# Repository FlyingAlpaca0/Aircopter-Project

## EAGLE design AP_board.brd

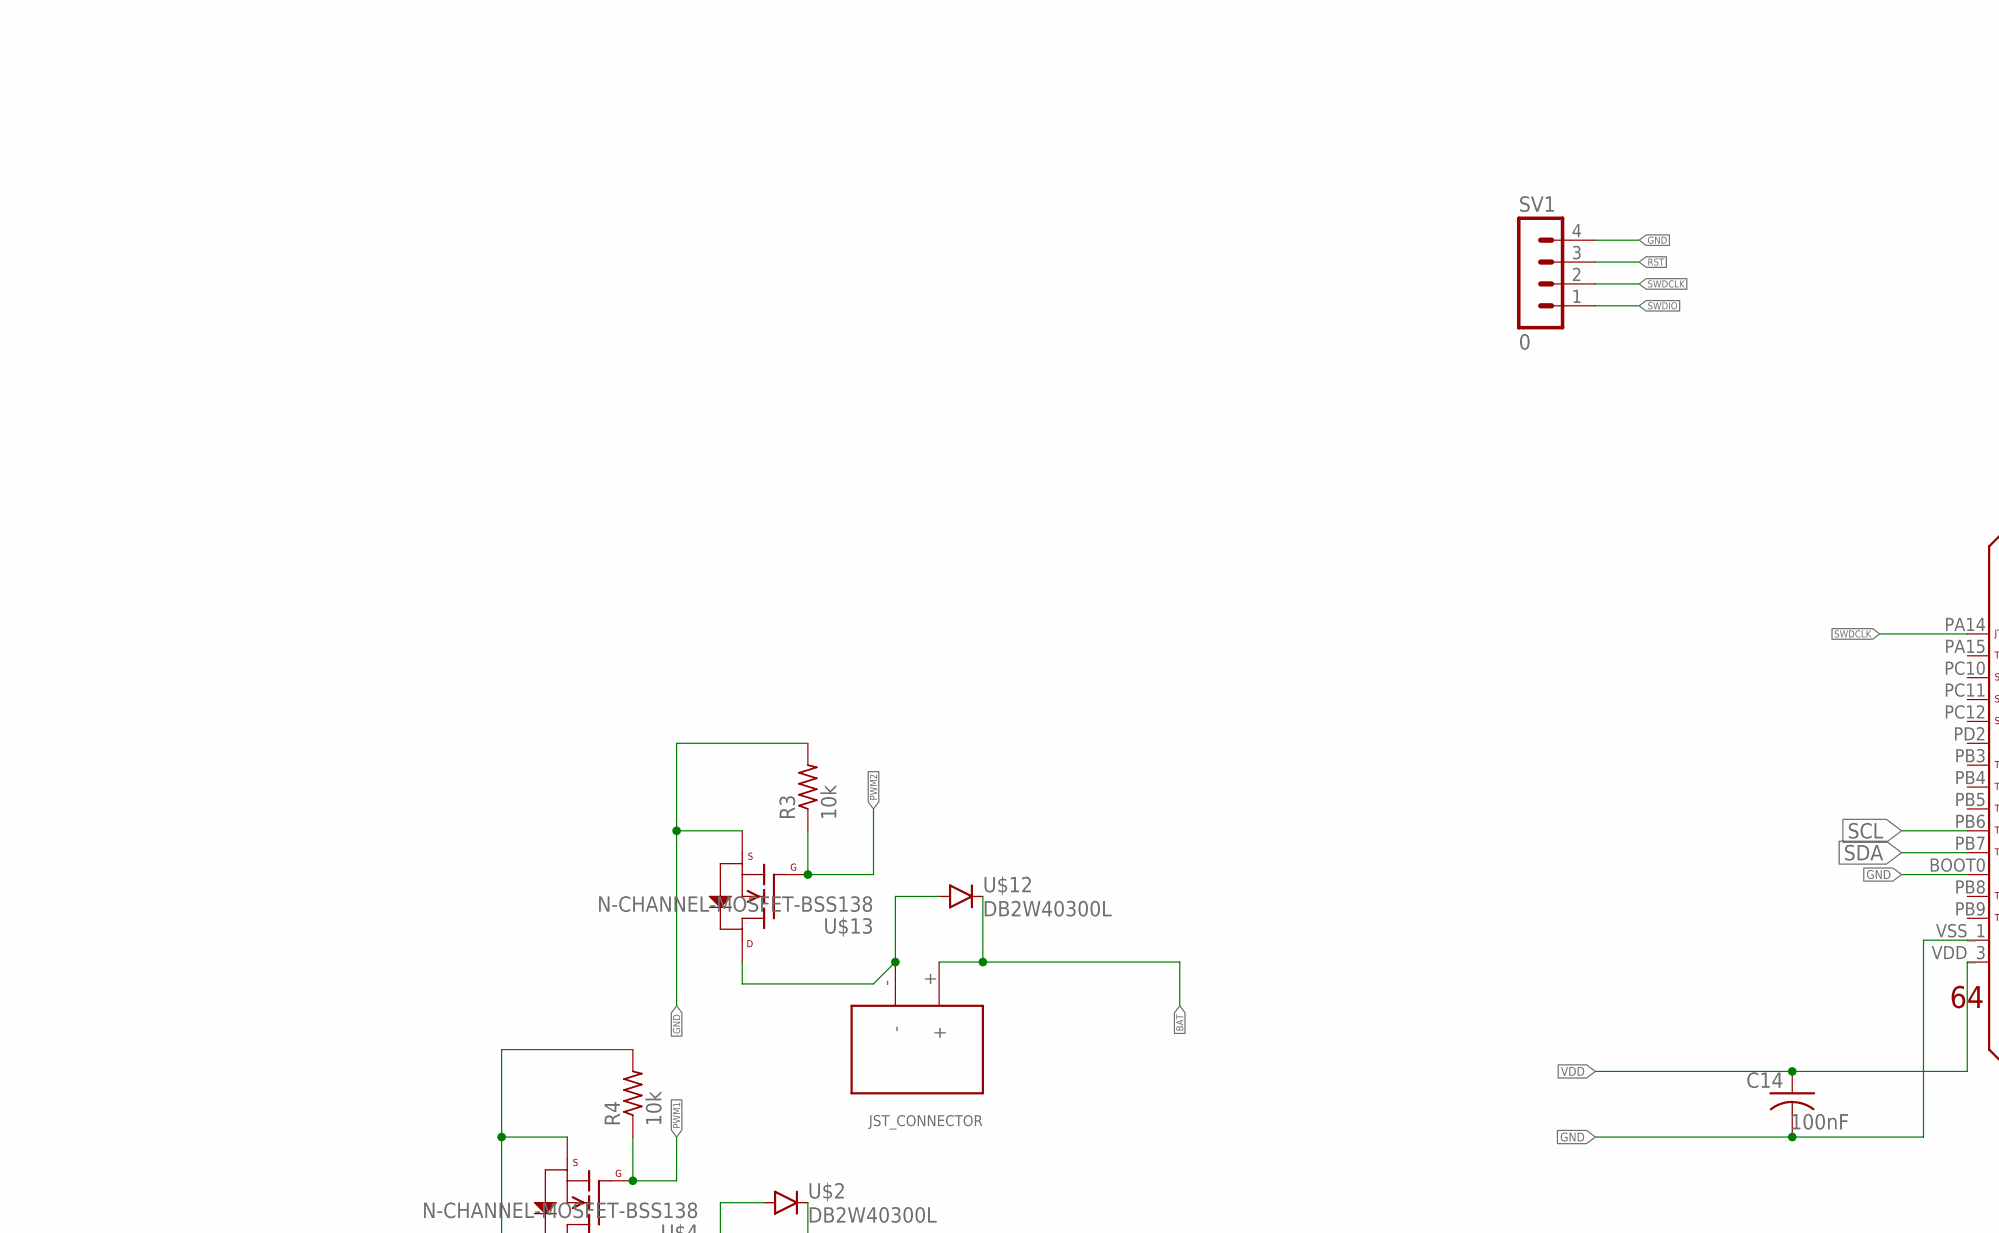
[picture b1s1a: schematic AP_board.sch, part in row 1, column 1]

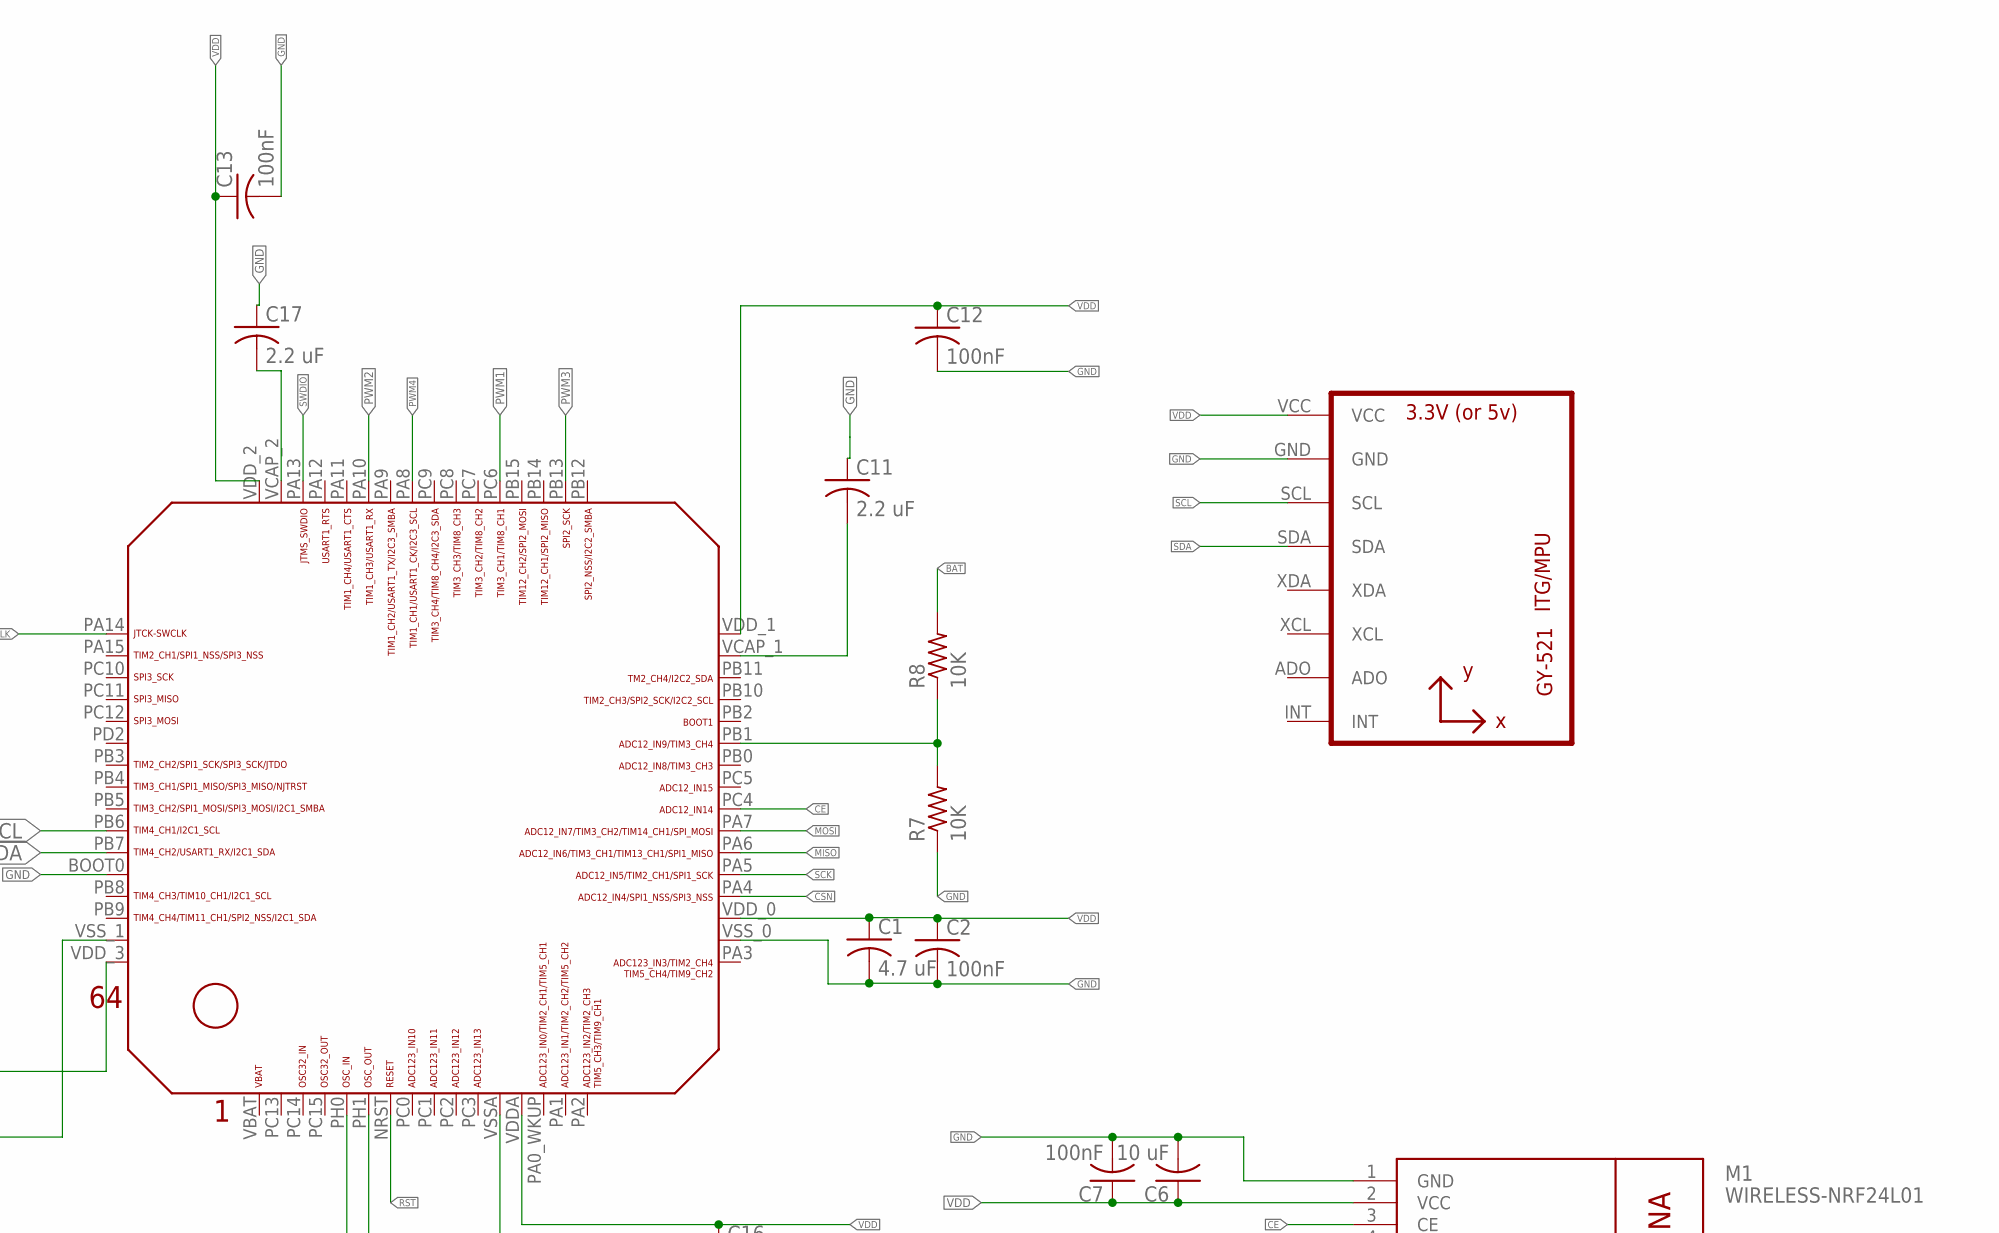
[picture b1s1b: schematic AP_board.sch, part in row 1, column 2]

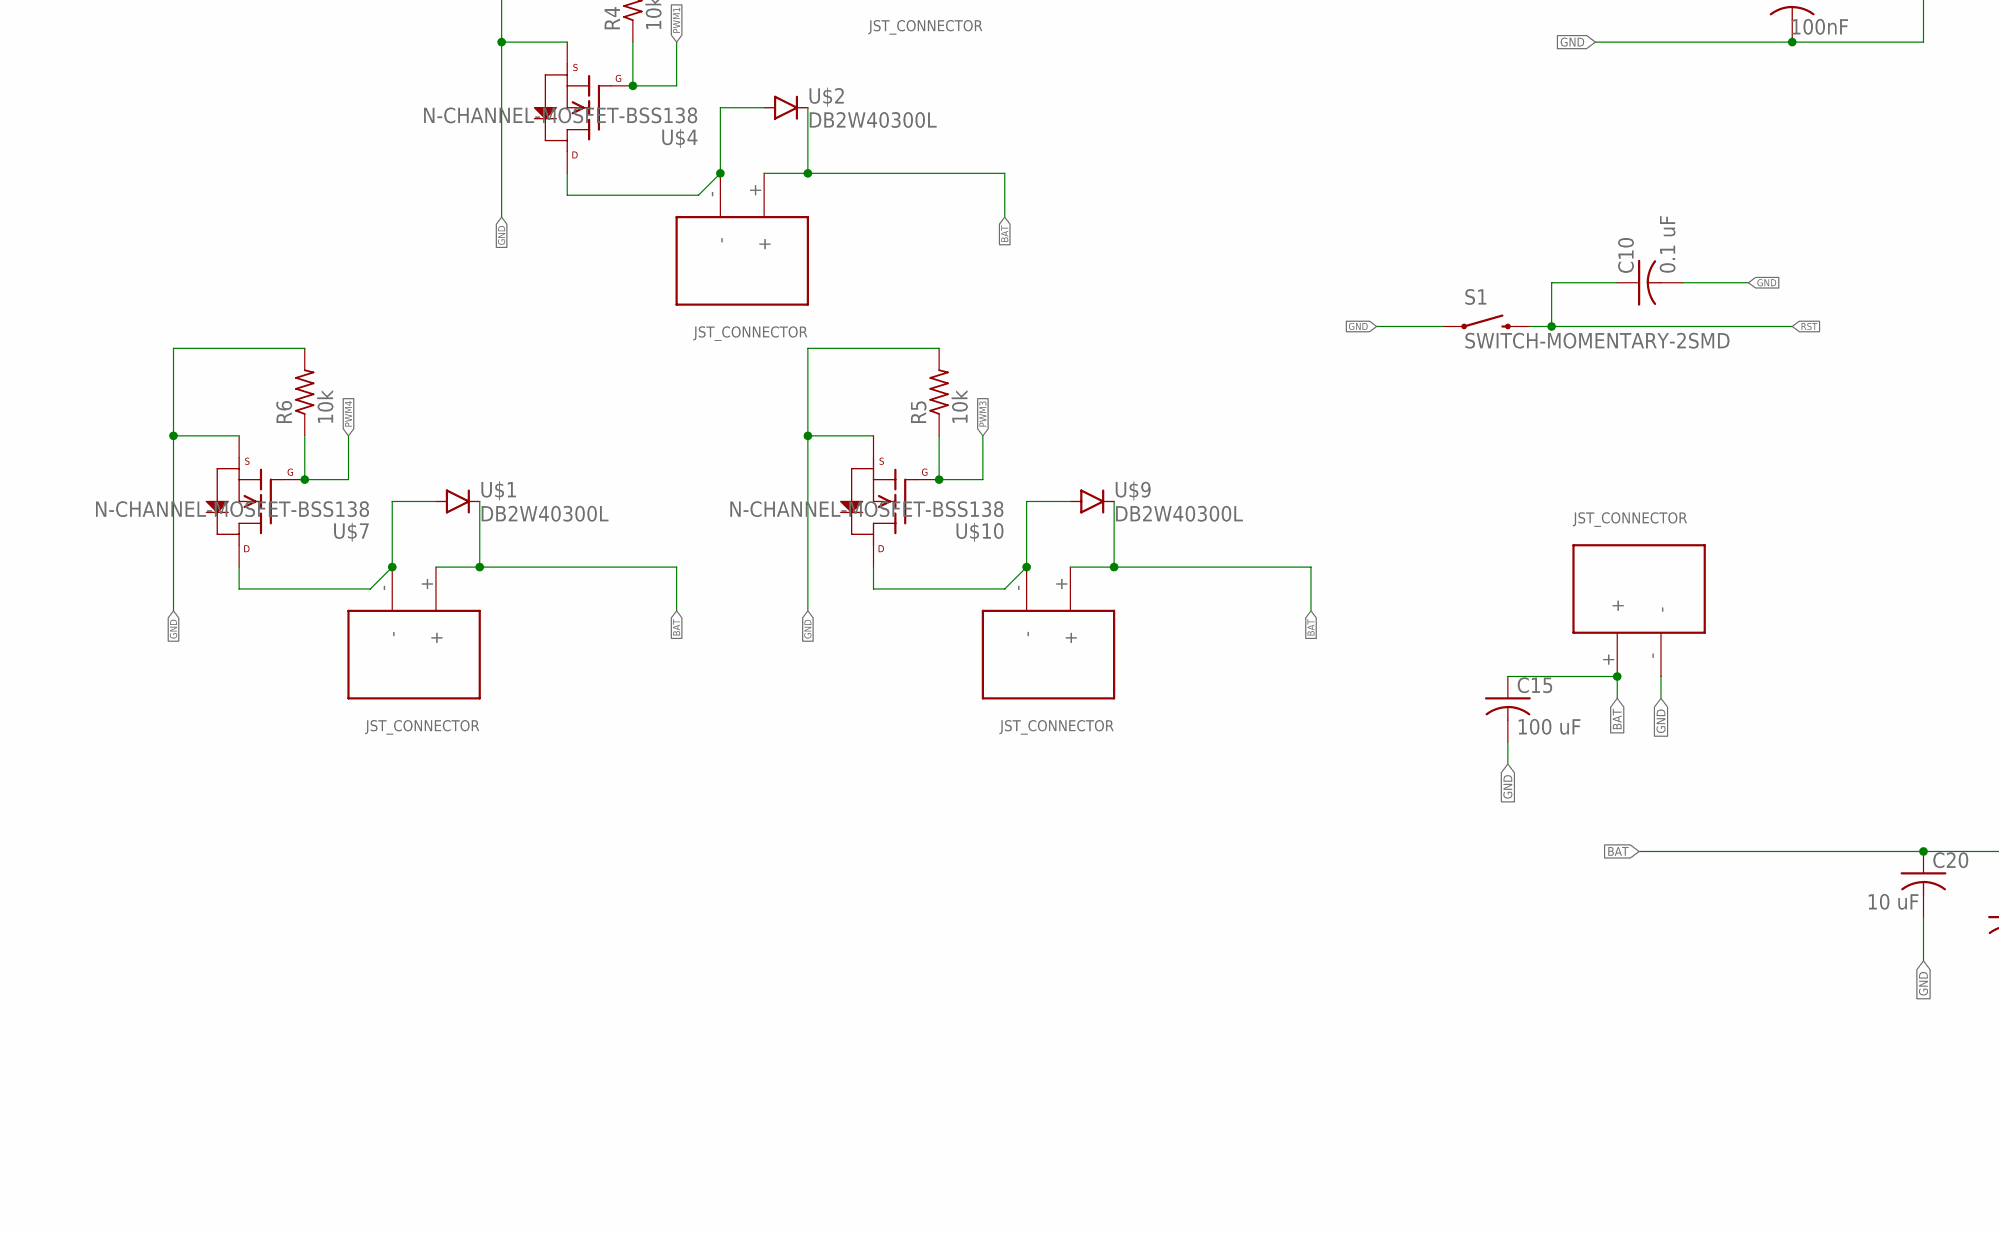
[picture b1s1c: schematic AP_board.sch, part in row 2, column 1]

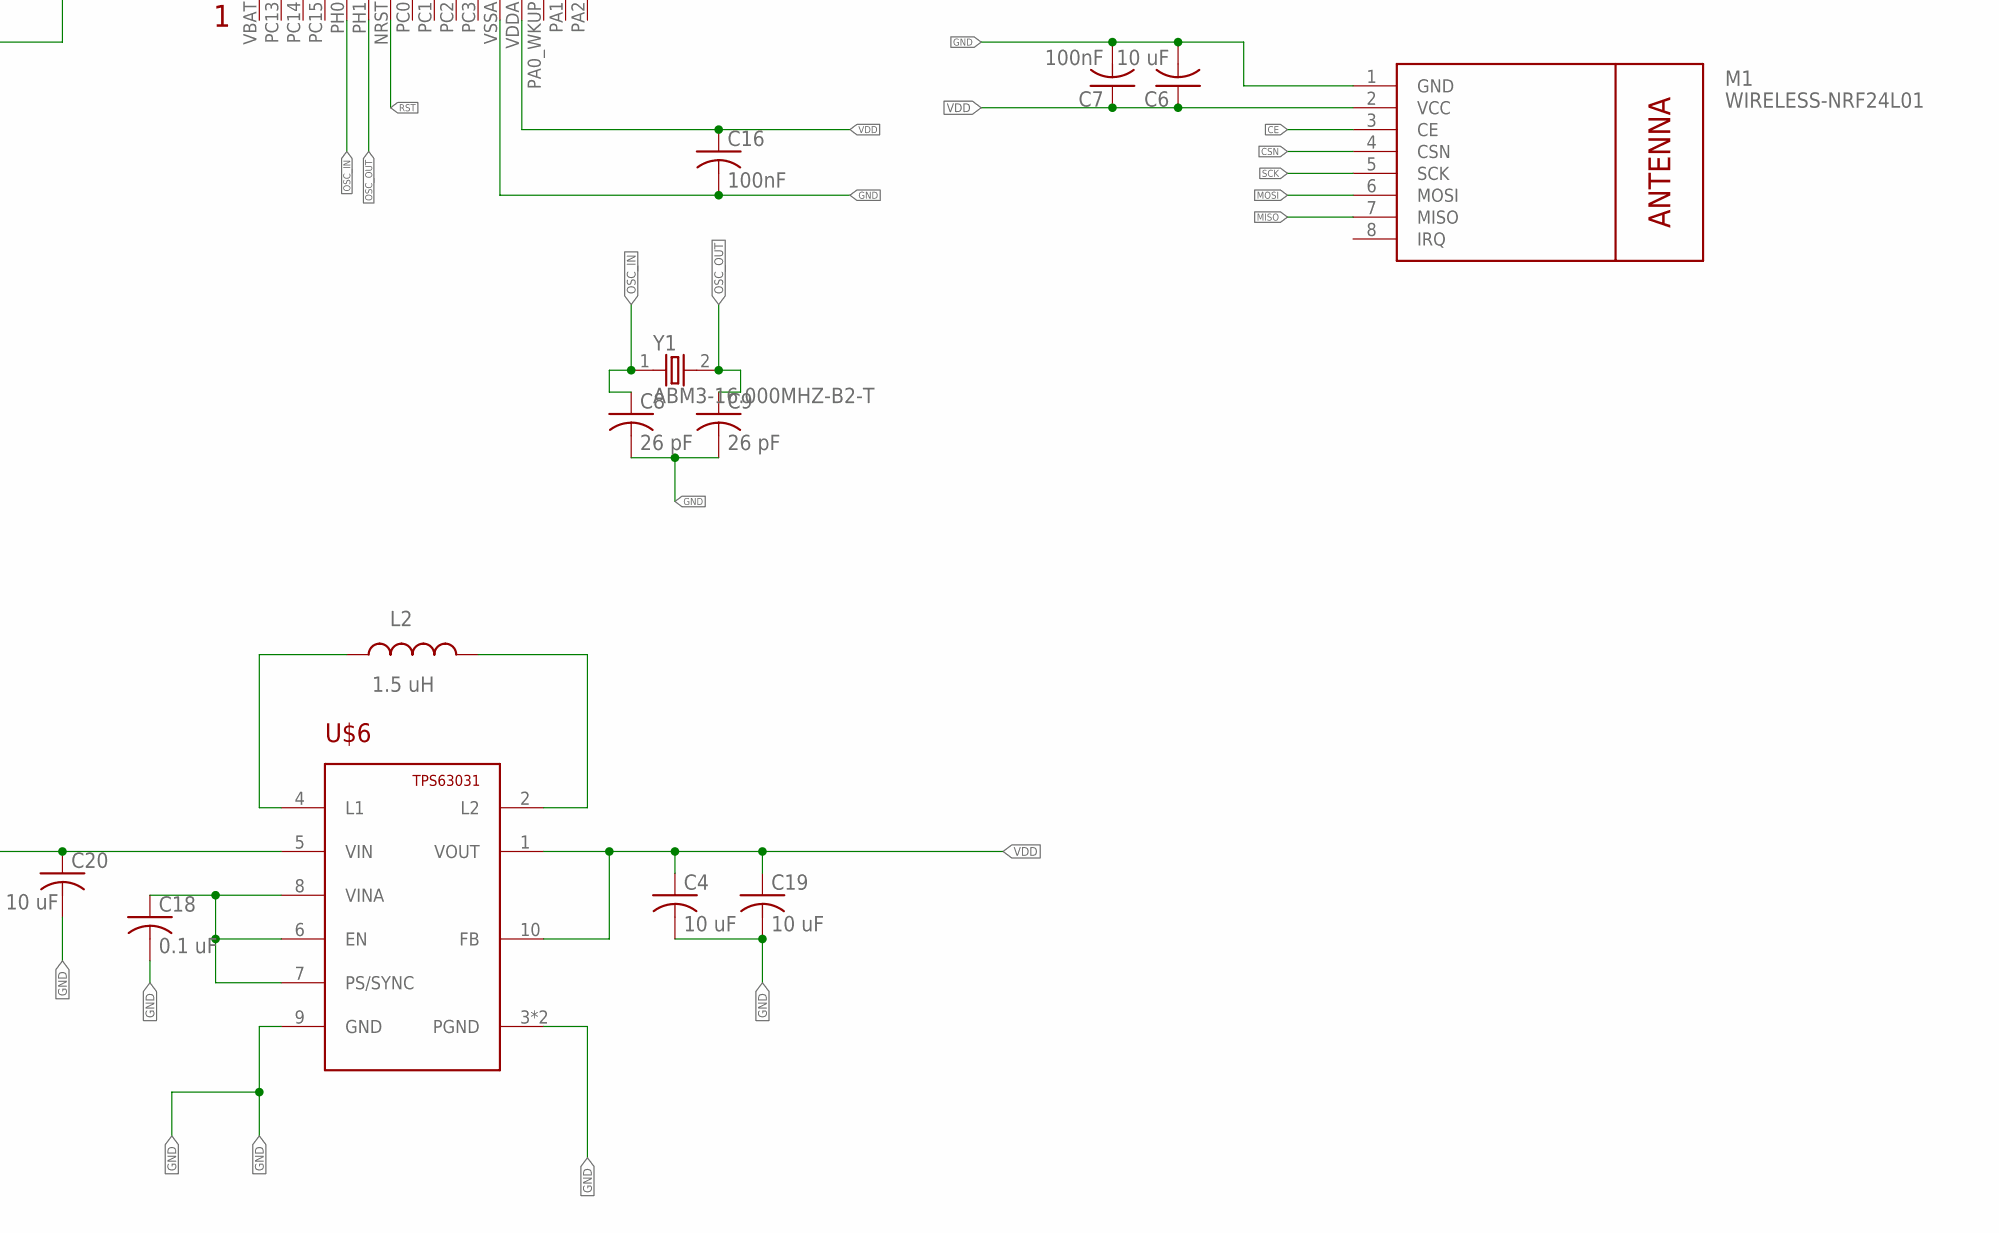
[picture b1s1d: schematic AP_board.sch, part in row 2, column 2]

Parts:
C1: 4.7 uF; C0603
C2, C7, C12, C13, C14, C16: 100nF; C0603
C4, C6, C19, C20: 10 uF; C0603
C8, C9: 26 pF; C0603
C10, C18: 0.1 uF; C0603
C11, C17: 2.2 uF; C0603
C15: 100 uF; C1206
L2: 1.5 uH; IND1212
M1: WIRELESS-NRF24L01
R3, R4, R5, R6: 10k; R0603
R7, R8: 10K; R0603
S1: SWITCH-MOMENTARY-2SMD; TACTILE-SWITCH-SMD
SV1: 0; MA04-1
U1: GY-521MPU6050; GY-521
U$1, U$2, U$9, U$12: DB2W40300L; MINI2-F3-B
U$3: STM32F405/415_LQFP64
U$4, U$7, U$10, U$13: N-CHANNEL-MOSFET-BSS138; SOT23-3
U$5, U$8, U$11, U$14, U$17: JST_CONNECTOR_FEMALE
U$6: TPS63031; SON-10
Y1: ABM3-16.000MHZ-B2-T; XTAL500X320X130N

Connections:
BAT: C15.1, C20.1, R8.2, U$1.NEG (GPIN), U$2.NEG (GPIN), U$5.+, U$6.5 (VIN), U$8.+, U$9.NEG (GPIN), U$11.+, U$12.NEG (GPIN), U$14.+, U$17.+
CE: M1.3 (CE), U$3.PC4
CSN: M1.4 (CSN), U$3.PA4
GND: C1.2, C2.2, C4.2, C6.2, C7.2, C8.2, C9.2, C10.2, C11.1, C12.2, C13.2, C14.2, C15.2, C16.2, C17.1, C18.2, C19.2, C20.2, M1.1 (GND), R3.2, R4.2, R5.2, R6.2, R7.1, S1.1, SV1.4, U1.GND, U$3.BOOT0, U$3.VSSA, U$3.VSS_0, U$3.VSS_1, U$4.2 (S), U$6.3 (PGND), U$6.9 (GND), U$6.PAD (PGND), U$7.2 (S), U$10.2 (S), U$13.2 (S), U$17.-
L3: L2.P$1 (1), U$6.4 (L1)
L4: L2.P$2 (2), U$6.2 (L2)
MISO: M1.7 (MISO), U$3.PA6
MOSI: M1.6 (MOSI), U$3.PA7
unnamed: U$2.POS (PPIN), U$4.3 (D), U$5.-
unnamed: U$1.POS (PPIN), U$7.3 (D), U$8.-
unnamed: U$9.POS (PPIN), U$10.3 (D), U$11.-
unnamed: U$12.POS (PPIN), U$13.3 (D), U$14.-
unnamed: C11.2, U$3.VCAP_1
unnamed: R7.2, R8.1, U$3.PB1
unnamed: C17.2, U$3.VCAP_2
unnamed: C18.1, U$6.6 (EN), U$6.7 (PS/SYNC), U$6.8 (VINA)
OSC_IN: C8.1, U$3.PH0, Y1.1
OSC_OUT: C9.1, U$3.PH1, Y1.2
PWM1: R4.1, U$3.PC6, U$4.1 (G)
PWM2: R3.1, U$3.PA10, U$13.1 (G)
PWM3: R5.1, U$3.PB13, U$10.1 (G)
PWM4: R6.1, U$3.PA8, U$7.1 (G)
RST: C10.1, S1.3 (2), SV1.3, U$3.NRST
SCK: M1.5 (SCK), U$3.PA5
SCL: U1.SCL, U$3.PB6
SDA: U1.SDA, U$3.PB7
SWDCLK: SV1.2, U$3.PA14
SWDIO: SV1.1, U$3.PA13
VDD: C1.1, C2.1, C4.1, C6.1, C7.1, C12.1, C13.1, C14.1, C16.1, C19.1, M1.2 (VCC), U1.VCC, U$3.VDDA, U$3.VDD_0, U$3.VDD_1, U$3.VDD_2, U$3.VDD_3, U$6.1 (VOUT), U$6.10 (FB)

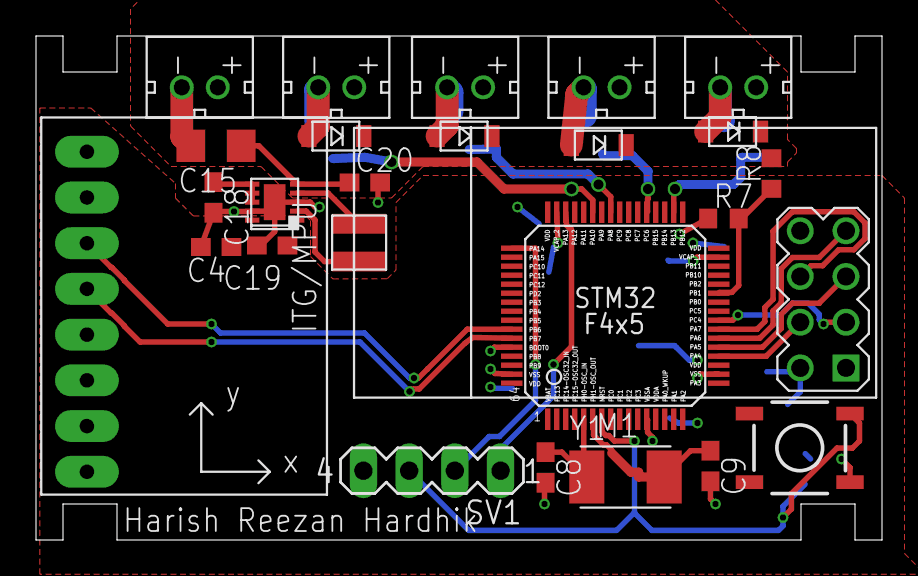
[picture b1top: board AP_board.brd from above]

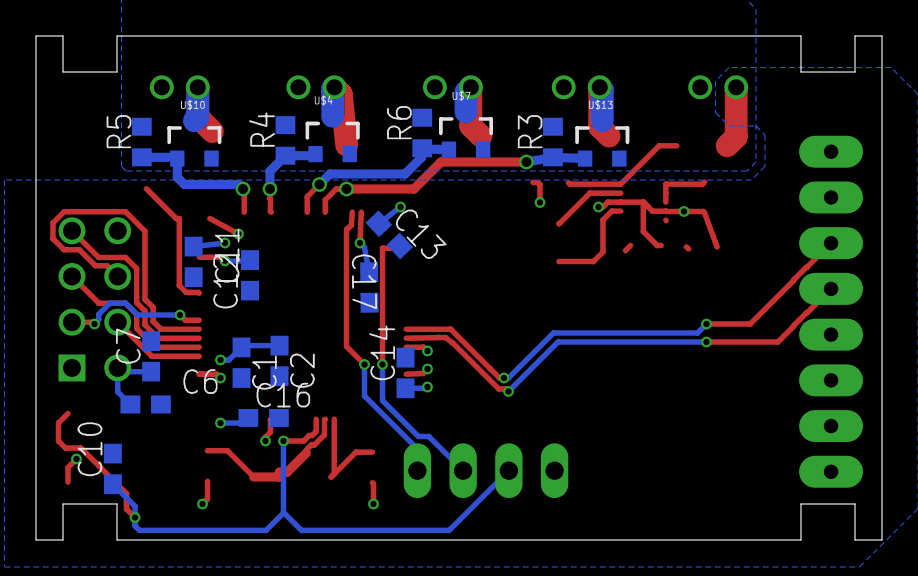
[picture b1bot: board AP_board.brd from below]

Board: 2 copper layers, 47.0 x 28.0 mm, 45 parts (19 on the bottom side), 29 nets.
